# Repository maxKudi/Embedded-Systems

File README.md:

# Embedded-Systems
An embedded system is a microprocessor-based computer hardware system with software that is designed to perform a dedicated function, either as an independent system or as a part of a large system. At the core is an integrated circuit designed to carry out computation for real-time operations.

# TinkerCAD 
https://www.tinkercad.com/users/5J5ShgS4AvR-chukwudi-okerulu

# KiCAD

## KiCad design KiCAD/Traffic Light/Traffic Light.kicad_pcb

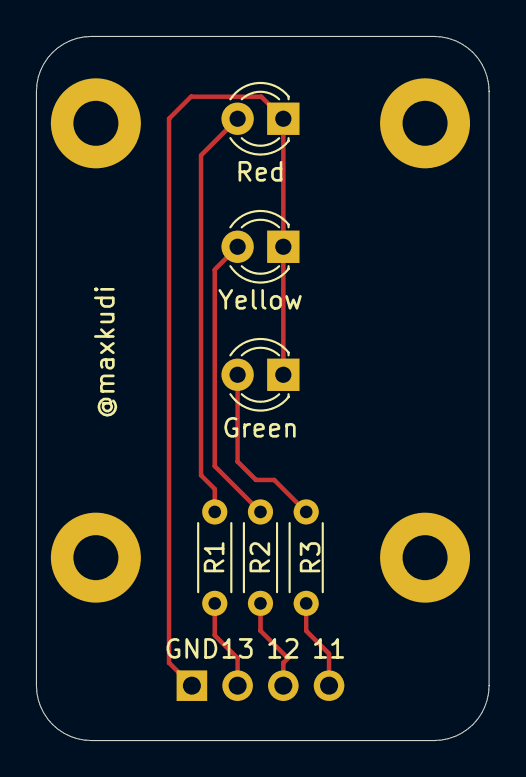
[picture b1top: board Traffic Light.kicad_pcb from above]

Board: 2 copper layers, 25.1 x 39.1 mm, 11 parts (1 on the bottom side), 7 nets.

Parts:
 : MountingHole; MountingHole_2.5mm_Pad
 #2,  #3,  #4: MountingHole; MountingHole_2.5mm_Pad
Green: LED; LED_D3.0mm
J1: Conn_01x04; PinHeader_1x04_P2.54mm_Horizontal
R1, R2, R3: R; R_Axial_DIN0204_L3.6mm_D1.6mm_P5.08mm_Horizontal
Red: LED; LED_D3.0mm
Yellow: LED; LED_D3.0mm

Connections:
unnamed: Green.1, J1.1, Red.1, Yellow.1
unnamed: R1.1, Red.2
unnamed: R2.1, Yellow.2
unnamed: Green.2, R3.1
unnamed: J1.2, R1.2
unnamed: J1.3, R2.2
unnamed: J1.4, R3.2

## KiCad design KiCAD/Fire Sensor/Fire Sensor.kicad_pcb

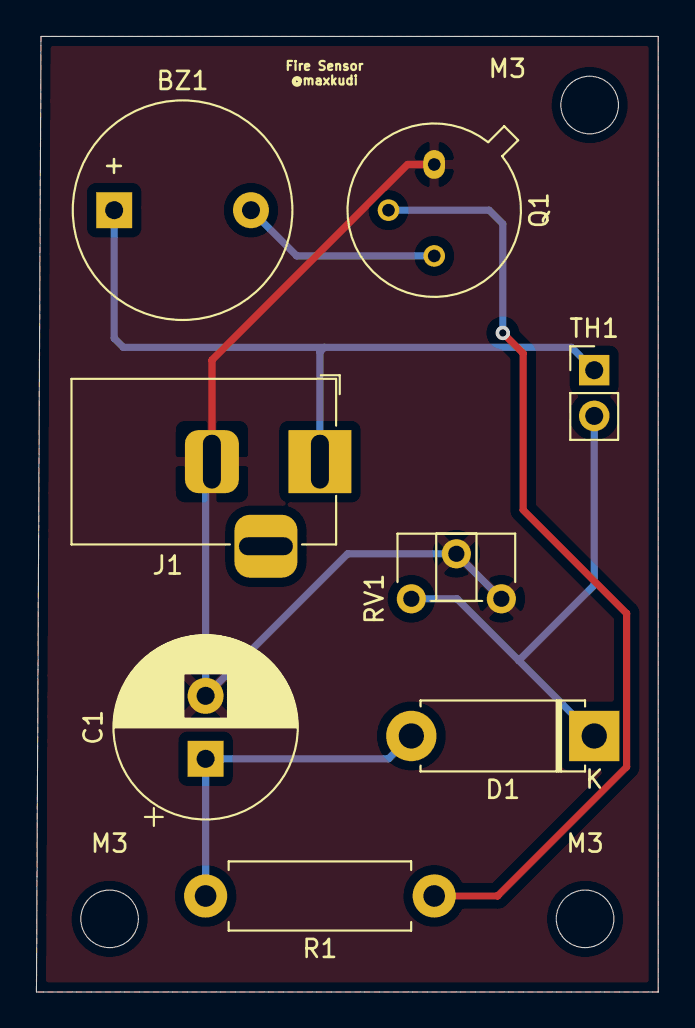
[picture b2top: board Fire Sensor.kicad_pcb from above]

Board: 2 copper layers, 34.5 x 53.1 mm, 11 parts (0 on the bottom side), 6 nets.

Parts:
BZ1: Buzzer; Buzzer_12x9.5RM7.6
C1: 10uF; CP_Radial_D10.0mm_P3.50mm
D1: 1N4007; D_5W_P10.16mm_Horizontal
J1: DC; BarrelJack_Horizontal
M3, M3#2, M3#3: MountingHole_3.2mm_M3
Q1: 2N2219; TO-39-3
R1: 33K; R_Axial_DIN0411_L9.9mm_D3.6mm_P12.70mm_Horizontal
RV1: 5K; Potentiometer_ACP_CA6-H2,5_Horizontal
TH1: 5K; PinHeader_1x02_P2.54mm_Vertical

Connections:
unnamed: BZ1.1, J1.1, TH1.1
unnamed: BZ1.2, Q1.3
unnamed: C1.1, D1.2, R1.2
unnamed: C1.2, J1.2, Q1.1, RV1.2, RV1.3
unnamed: D1.1, RV1.1, TH1.2
unnamed: Q1.2, R1.1

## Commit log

2020-12-21 Added Fire Sensor Project
2020-12-21 Added Traffic Light Project
2021-09-01 Added LinkedIn Certificate
